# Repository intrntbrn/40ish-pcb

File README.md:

40-ish (a Bakeneko60 fork)
==================

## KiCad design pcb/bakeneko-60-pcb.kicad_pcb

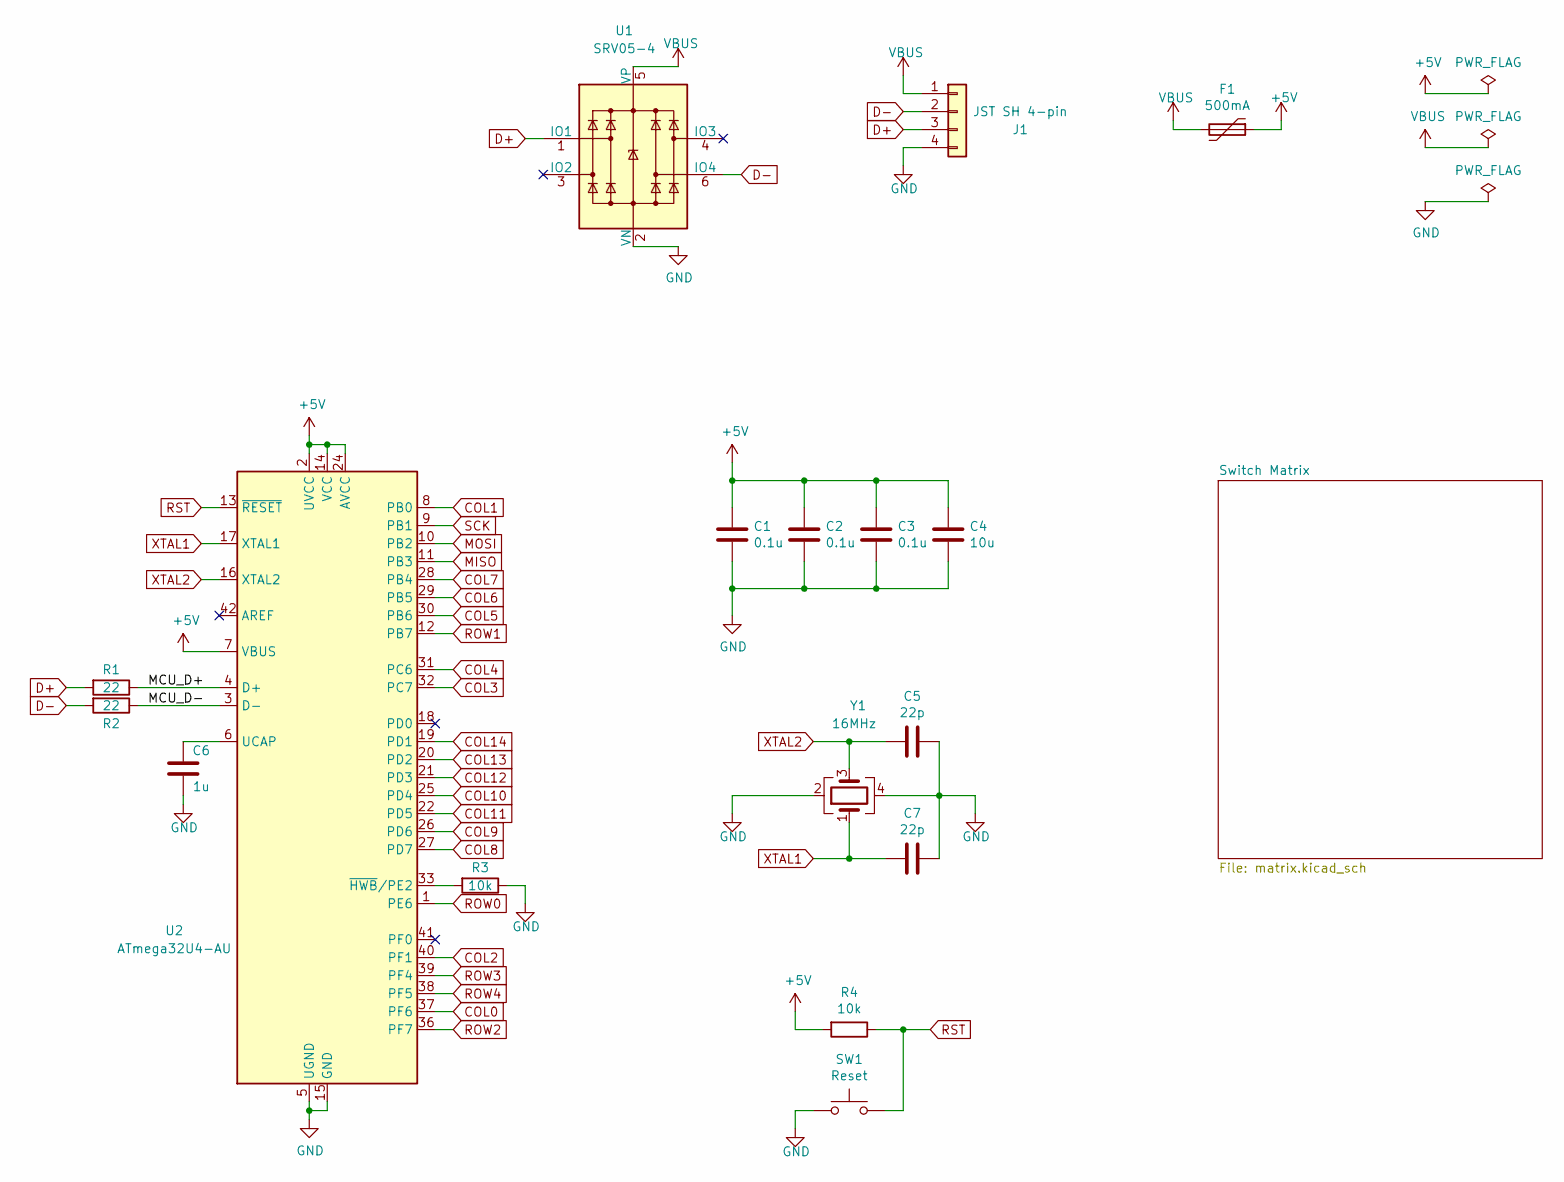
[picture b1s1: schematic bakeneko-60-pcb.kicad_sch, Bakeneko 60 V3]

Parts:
C1, C2, C3: 0.1u; C_0805_2012Metric; LCSC Part # C49678
C4: 10u; C_0805_2012Metric; LCSC Part # C15850
C5, C7: 22p; C_0805_2012Metric; LCSC Part # C1804
C6: 1u; C_0805_2012Metric; LCSC Part # C28323
F1: 500mA; Fuse_1206_3216Metric; LCSC Part # C70076
J1: JST SH 4-pin; JST_SH_SM04B-SRSS-TB_1x04-1MP_P1.00mm_Horizontal; LCSC Part # C160404
R1, R2: 22; R_0805_2012Metric; LCSC Part # C17561
R3, R4: 10k; R_0805_2012Metric; LCSC Part # C17414
SW1: Reset; SW_SPST_TL3342; LCSC Part # C318884
U1: SRV05-4; SOT-23-6; LCSC Part # C85364
U2: ATmega32U4-AU; TQFP-44_10x10mm_P0.8mm; LCSC Part # C44854
Y1: 16MHz; Crystal_SMD_3225-4Pin_3.2x2.5mm; LCSC Part # C13738

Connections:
+5V: C1.1, C2.1, C3.1, C4.1, F1.1, R4.2, U2.2 (UVCC), U2.7 (VBUS), U2.14 (VCC), U2.24 (AVCC), U2.34 (VCC), U2.44 (AVCC)
/MCU_D+: R1.1, U2.4 (D+)
/MCU_D-: R2.1, U2.3 (D-)
COL0: U2.37 (PF6); also elsewhere on the board
COL1: U2.8 (PB0); also elsewhere on the board
COL2: U2.40 (PF1); also elsewhere on the board
COL3: U2.32 (PC7); also elsewhere on the board
COL4: U2.31 (PC6); also elsewhere on the board
COL5: U2.30 (PB6); also elsewhere on the board
COL6: U2.29 (PB5); also elsewhere on the board
COL7: U2.28 (PB4); also elsewhere on the board
COL8: U2.27 (PD7); also elsewhere on the board
COL9: U2.26 (PD6); also elsewhere on the board
COL10: U2.25 (PD4); also elsewhere on the board
COL11: U2.22 (PD5); also elsewhere on the board
COL12: U2.21 (PD3); also elsewhere on the board
COL13: U2.20 (PD2); also elsewhere on the board
COL14: U2.19 (PD1); also elsewhere on the board
D+: J1.3, R1.2, U1.1 (IO1)
D-: J1.2, R2.2, U1.6 (IO4)
GND: C1.2, C2.2, C3.2, C4.2, C5.1, C6.2, C7.1, J1.4, R3.1, SW1.1, U1.2 (VN), U2.5 (UGND), U2.15 (GND), U2.23 (GND), U2.35 (GND), U2.43 (GND), Y1.2, Y1.4
MISO: U2.11 (PB3)
MOSI: U2.10 (PB2)
unnamed: C6.1, U2.6 (UCAP)
unnamed: R3.2, U2.33 (~HWB/PE2)
ROW0: U2.1 (PE6); also elsewhere on the board
ROW1: U2.12 (PB7); also elsewhere on the board
ROW2: U2.36 (PF7); also elsewhere on the board
ROW3: U2.39 (PF4); also elsewhere on the board
ROW4: U2.38 (PF5); also elsewhere on the board
RST: R4.1, SW1.2, U2.13 (~RESET)
SCK: U2.9 (PB1)
VBUS: F1.2, J1.1, U1.5 (VP)
XTAL1: C7.2, U2.17 (XTAL1), Y1.1
XTAL2: C5.2, U2.16 (XTAL2), Y1.3

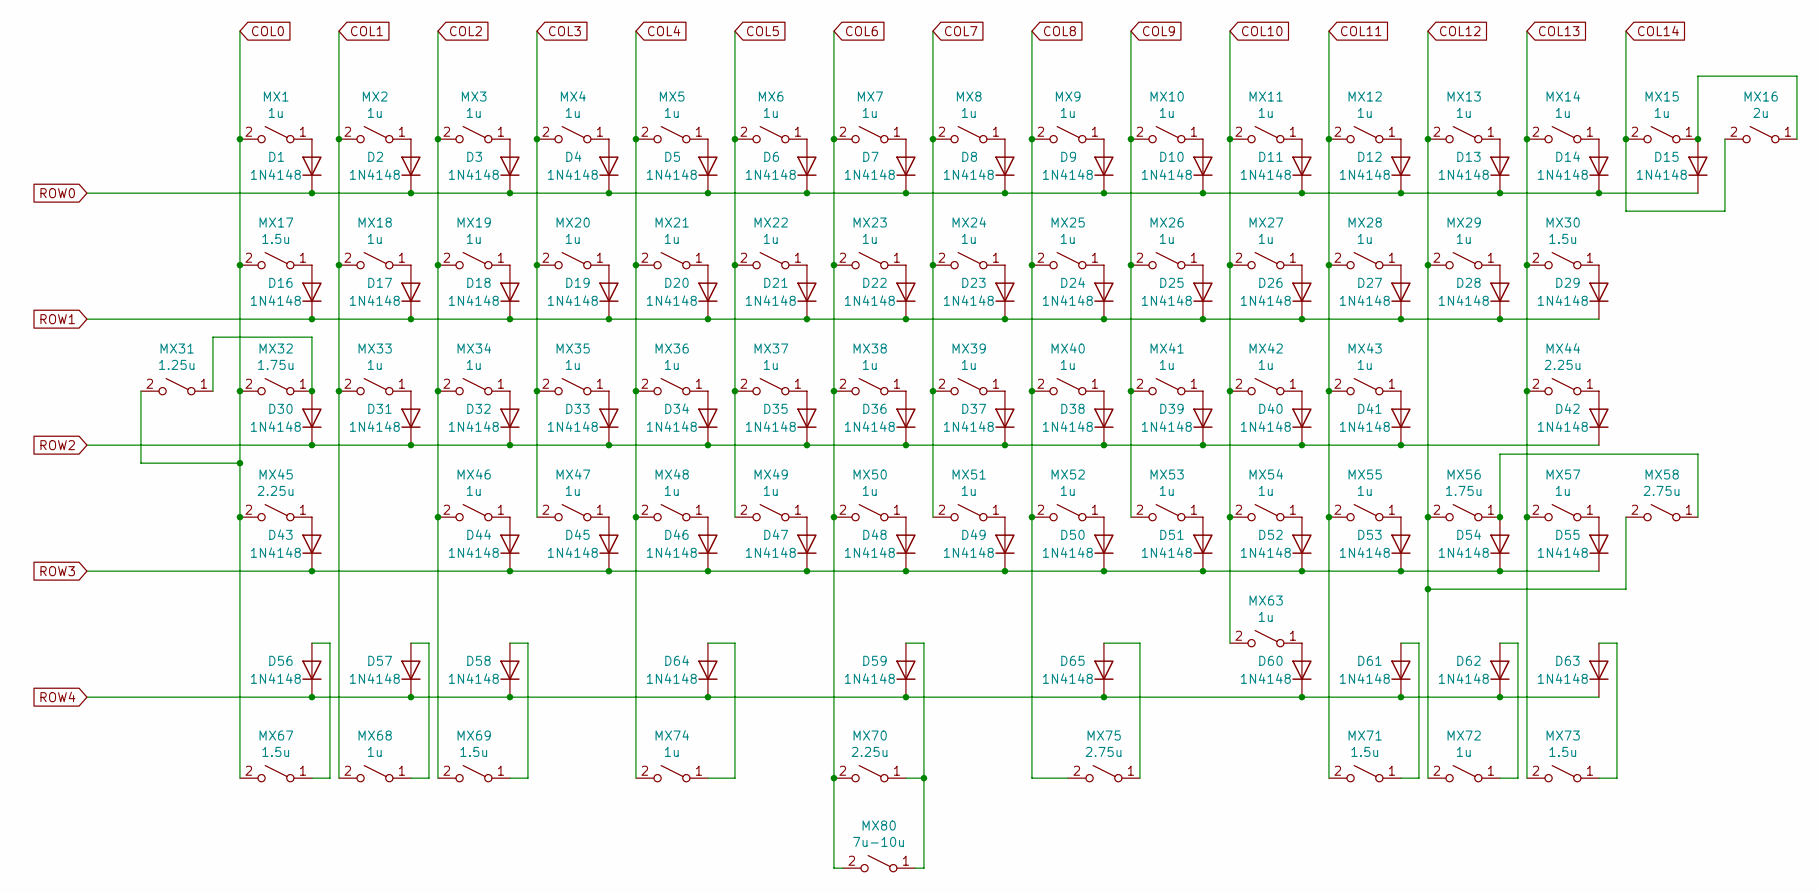
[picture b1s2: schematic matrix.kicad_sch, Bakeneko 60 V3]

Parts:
D1, D2, D3, D4, D5, D6, D7, D8, D9, D10, D11, D12, D13, D14, D15, D16, D17, D18, D19, D20, D21, D22, D23, D24, D25, D26, D27, D28, D29, D30, D31, D32, D33, D34, D35, D36, D37, D38, D39, D40, D41, D42, D43, D44, D45, D46, D47, D48, D49, D50, D51, D52, D53, D54, D55, D56, D57, D58, D59, D60, D61, D62, D63, D64, D65: 1N4148; D_SOD-123; LCSC Part # C81598
MX1, MX2, MX3, MX4, MX5, MX6, MX7, MX8, MX9, MX10, MX11, MX12, MX13, MX14, MX15, MX18, MX19, MX20, MX21, MX22, MX23, MX24, MX25, MX26, MX27, MX28, MX29, MX33, MX34, MX35, MX36, MX37, MX38, MX39, MX40, MX41, MX42, MX43, MX46, MX47, MX48, MX49, MX50, MX51, MX52, MX53, MX54, MX55, MX57, MX63, MX68, MX72, MX74: 1u; MXOnly-1U-NoLED
MX16: 2u; MXOnly-2U-NoLED
MX17, MX30, MX67, MX69, MX71, MX73: 1.5u; MXOnly-1.5U-NoLED
MX31: 1.25u; MXOnly-1.25U-NoLED
MX32, MX56: 1.75u; MXOnly-1.75U-NoLED
MX44, MX45: 2.25u; MXOnly-2.25U-NoLED
MX58: 2.75u; MXOnly-2.75U-NoLED
MX70: 2.25u; MXOnly-2.25U-ReversedStabilizers-NoLED
MX75: 2.75u; MXOnly-2.75U-ReversedStabilizers-NoLED
MX80: 7u-10u; MXOnly-10U-7U-ReversedStabilizers-NoLED

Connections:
COL0: MX1.2 (B), MX17.2 (B), MX31.2 (B), MX32.2 (B), MX45.2 (B), MX67.2 (B); also elsewhere on the board
COL1: MX2.2 (B), MX18.2 (B), MX33.2 (B), MX68.2 (B); also elsewhere on the board
COL2: MX3.2 (B), MX19.2 (B), MX34.2 (B), MX46.2 (B), MX69.2 (B); also elsewhere on the board
COL3: MX4.2 (B), MX20.2 (B), MX35.2 (B), MX47.2 (B); also elsewhere on the board
COL4: MX5.2 (B), MX21.2 (B), MX36.2 (B), MX48.2 (B), MX74.2 (B); also elsewhere on the board
COL5: MX6.2 (B), MX22.2 (B), MX37.2 (B), MX49.2 (B); also elsewhere on the board
COL6: MX7.2 (B), MX23.2 (B), MX38.2 (B), MX50.2 (B), MX70.2 (B), MX80.2 (B); also elsewhere on the board
COL7: MX8.2 (B), MX24.2 (B), MX39.2 (B), MX51.2 (B); also elsewhere on the board
COL8: MX9.2 (B), MX25.2 (B), MX40.2 (B), MX52.2 (B), MX75.2 (B); also elsewhere on the board
COL9: MX10.2 (B), MX26.2 (B), MX41.2 (B), MX53.2 (B); also elsewhere on the board
COL10: MX11.2 (B), MX27.2 (B), MX42.2 (B), MX54.2 (B), MX63.2 (B); also elsewhere on the board
COL11: MX12.2 (B), MX28.2 (B), MX43.2 (B), MX55.2 (B), MX71.2 (B); also elsewhere on the board
COL12: MX13.2 (B), MX29.2 (B), MX56.2 (B), MX58.2 (B), MX72.2 (B); also elsewhere on the board
COL13: MX14.2 (B), MX30.2 (B), MX44.2 (B), MX57.2 (B), MX73.2 (B); also elsewhere on the board
COL14: MX15.2 (B), MX16.2 (B); also elsewhere on the board
unnamed: D1.2 (A), MX1.1 (A)
unnamed: D2.2 (A), MX2.1 (A)
unnamed: D3.2 (A), MX3.1 (A)
unnamed: D4.2 (A), MX4.1 (A)
unnamed: D5.2 (A), MX5.1 (A)
unnamed: D6.2 (A), MX6.1 (A)
unnamed: D7.2 (A), MX7.1 (A)
unnamed: D8.2 (A), MX8.1 (A)
unnamed: D9.2 (A), MX9.1 (A)
unnamed: D10.2 (A), MX10.1 (A)
unnamed: D11.2 (A), MX11.1 (A)
unnamed: D12.2 (A), MX12.1 (A)
unnamed: D13.2 (A), MX13.1 (A)
unnamed: D14.2 (A), MX14.1 (A)
unnamed: D15.2 (A), MX15.1 (A), MX16.1 (A)
unnamed: D16.2 (A), MX17.1 (A)
unnamed: D17.2 (A), MX18.1 (A)
unnamed: D18.2 (A), MX19.1 (A)
unnamed: D19.2 (A), MX20.1 (A)
unnamed: D20.2 (A), MX21.1 (A)
unnamed: D21.2 (A), MX22.1 (A)
unnamed: D22.2 (A), MX23.1 (A)
unnamed: D23.2 (A), MX24.1 (A)
unnamed: D24.2 (A), MX25.1 (A)
unnamed: D25.2 (A), MX26.1 (A)
unnamed: D26.2 (A), MX27.1 (A)
unnamed: D27.2 (A), MX28.1 (A)
unnamed: D28.2 (A), MX29.1 (A)
unnamed: D29.2 (A), MX30.1 (A)
unnamed: D30.2 (A), MX31.1 (A), MX32.1 (A)
unnamed: D31.2 (A), MX33.1 (A)
unnamed: D32.2 (A), MX34.1 (A)
unnamed: D33.2 (A), MX35.1 (A)
unnamed: D34.2 (A), MX36.1 (A)
unnamed: D35.2 (A), MX37.1 (A)
unnamed: D36.2 (A), MX38.1 (A)
unnamed: D37.2 (A), MX39.1 (A)
unnamed: D38.2 (A), MX40.1 (A)
unnamed: D39.2 (A), MX41.1 (A)
unnamed: D40.2 (A), MX42.1 (A)
unnamed: D41.2 (A), MX43.1 (A)
unnamed: D42.2 (A), MX44.1 (A)
unnamed: D43.2 (A), MX45.1 (A)
unnamed: D44.2 (A), MX46.1 (A)
unnamed: D45.2 (A), MX47.1 (A)
unnamed: D46.2 (A), MX48.1 (A)
unnamed: D47.2 (A), MX49.1 (A)
unnamed: D48.2 (A), MX50.1 (A)
unnamed: D49.2 (A), MX51.1 (A)
unnamed: D50.2 (A), MX52.1 (A)
unnamed: D51.2 (A), MX53.1 (A)
unnamed: D52.2 (A), MX54.1 (A)
unnamed: D53.2 (A), MX55.1 (A)
unnamed: D54.2 (A), MX56.1 (A), MX58.1 (A)
unnamed: D55.2 (A), MX57.1 (A)
unnamed: D56.2 (A), MX67.1 (A)
unnamed: D57.2 (A), MX68.1 (A)
unnamed: D58.2 (A), MX69.1 (A)
unnamed: D59.2 (A), MX70.1 (A), MX80.1 (A)
unnamed: D60.2 (A), MX63.1 (A)
unnamed: D61.2 (A), MX71.1 (A)
unnamed: D62.2 (A), MX72.1 (A)
unnamed: D63.2 (A), MX73.1 (A)
unnamed: D64.2 (A), MX74.1 (A)
unnamed: D65.2 (A), MX75.1 (A)
ROW0: D1.1 (K), D2.1 (K), D3.1 (K), D4.1 (K), D5.1 (K), D6.1 (K), D7.1 (K), D8.1 (K), D9.1 (K), D10.1 (K), D11.1 (K), D12.1 (K), D13.1 (K), D14.1 (K), D15.1 (K); also elsewhere on the board
ROW1: D16.1 (K), D17.1 (K), D18.1 (K), D19.1 (K), D20.1 (K), D21.1 (K), D22.1 (K), D23.1 (K), D24.1 (K), D25.1 (K), D26.1 (K), D27.1 (K), D28.1 (K), D29.1 (K); also elsewhere on the board
ROW2: D30.1 (K), D31.1 (K), D32.1 (K), D33.1 (K), D34.1 (K), D35.1 (K), D36.1 (K), D37.1 (K), D38.1 (K), D39.1 (K), D40.1 (K), D41.1 (K), D42.1 (K); also elsewhere on the board
ROW3: D43.1 (K), D44.1 (K), D45.1 (K), D46.1 (K), D47.1 (K), D48.1 (K), D49.1 (K), D50.1 (K), D51.1 (K), D52.1 (K), D53.1 (K), D54.1 (K), D55.1 (K); also elsewhere on the board
ROW4: D56.1 (K), D57.1 (K), D58.1 (K), D59.1 (K), D60.1 (K), D61.1 (K), D62.1 (K), D63.1 (K), D64.1 (K), D65.1 (K); also elsewhere on the board

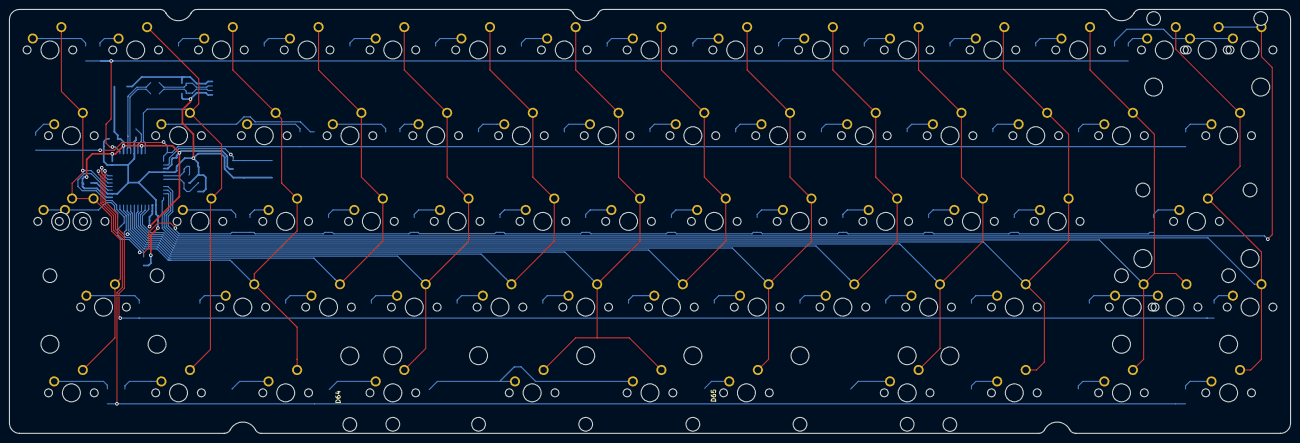
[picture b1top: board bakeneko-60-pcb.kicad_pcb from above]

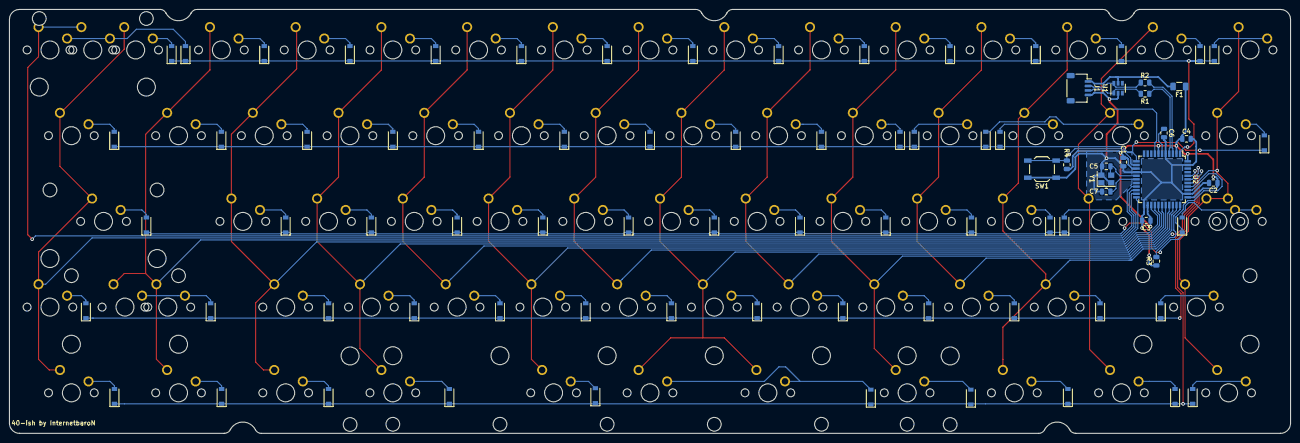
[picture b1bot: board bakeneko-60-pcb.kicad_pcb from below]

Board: 2 copper layers, 284.7 x 94.2 mm, 151 parts (82 on the bottom side), 97 nets.

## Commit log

2022-07-22 remove 6.25u bottom row
2022-07-22 add fn1
2022-07-22 bottom row done except for diodes wrong side
2022-07-22 bottom row done
2022-07-22 fix silkscreen diode text
2022-07-22 all good, waiting for outline
2022-07-22 cleanup readme
2022-07-22 add production files
2022-07-22 add qmk header
2022-07-22 fix qmk header indentation
2022-07-23 no corner outline
2022-07-23 remove silk overlay placeholder
2022-07-23 move text to center
2022-07-23 corner outline fix
2022-07-23 flip diode silk
2022-07-23 remove 2u bs option due to leaf spring interference
2022-07-23 pass drc checks
2022-07-23 align leaf spring holes properly
2022-07-23 round outline corners
2022-07-23 fine tune corners
2022-07-23 generate production files
2022-07-23 kle and pcb image
2022-07-25 move diode and make room for jst replacement
2022-07-25 remove isp and connections
2022-07-25 move jst connector
2022-07-25 micro adjust placement of jst connector
2022-07-25 cleanup tracks
2022-07-25 update renders
2022-07-25 update production files
2022-07-31 generic layout baseline
2022-07-31 remove isp

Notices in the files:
pcb/bakeneko-60-pcb.kicad_sch:
Copyright © 2020 kkatano
MIT License
